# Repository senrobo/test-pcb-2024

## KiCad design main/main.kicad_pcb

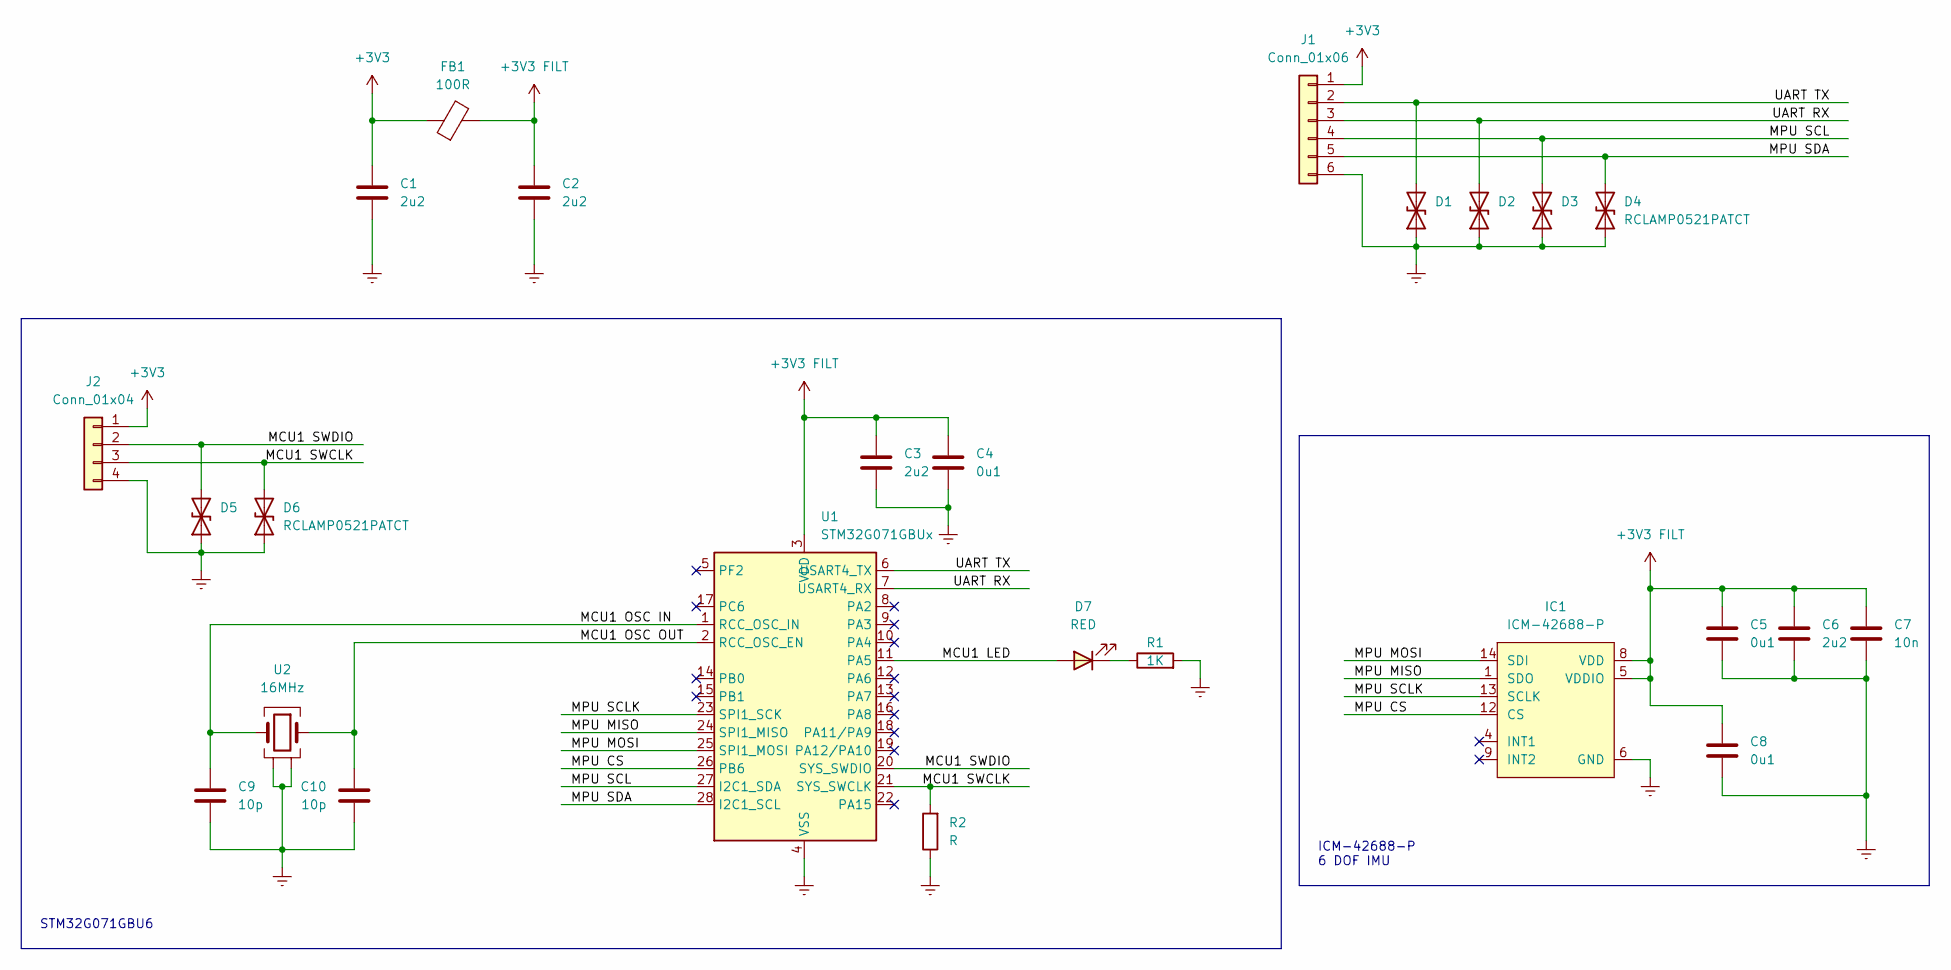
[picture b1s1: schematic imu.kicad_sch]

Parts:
C1, C2: 2u2; cap0603
C3, C6: 2u2; C_0402_1005Metric_Pad0.74x0.62mm_HandSolder
C4, C5, C8: 0u1; C_0402_1005Metric_Pad0.74x0.62mm_HandSolder
C7: 10n; C_0402_1005Metric_Pad0.74x0.62mm_HandSolder
C9, C10: 10p; C_0402_1005Metric_Pad0.74x0.62mm_HandSolder
D1, D2, D3, D4, D5, D6: RCLAMP0521PATCT
D7: RED; led0603
FB1: 100R; fb0603
IC1: ICM-42688-P; IIM42352; Mouser Part Number 410-ICM-42688-P
J1: Conn_01x06; PinHeader_1x06_P2.54mm_Vertical
J2: Conn_01x04; PinHeader_2x02_P2.54mm_Vertical
R1: 1K; R_0402_1005Metric
R2: R; R_0402_1005Metric
U1: STM32G071GBUx; QFN-28_4x4mm_P0.5mm
U2: 16MHz; 830108288709

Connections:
+3V3: C1.1, FB1.1, J1.1, J2.1
+3V3 FILT: C2.1, C3.1, C4.1, C5.1, C6.1, C7.1, C8.1, FB1.2, IC1.5 (VDDIO), IC1.8 (VDD), U1.3 (VDD)
/imu/MCU1 LED: D7.2 (A), U1.11 (PA5)
/imu/MCU1 OSC IN: C9.1, U1.1 (RCC_OSC_IN), U2.3
/imu/MCU1 OSC OUT: C10.1, U1.2 (RCC_OSC_EN), U2.1
/imu/MCU1 SWCLK: D6.2 (A2), J2.3, R2.2, U1.21 (SYS_SWCLK)
/imu/MCU1 SWDIO: D5.2 (A2), J2.2, U1.20 (SYS_SWDIO)
/imu/MPU CS: IC1.12 (CS), U1.26 (PB6)
/imu/MPU MISO: IC1.1 (SDO), U1.24 (SPI1_MISO)
/imu/MPU MOSI: IC1.14 (SDI), U1.25 (SPI1_MOSI)
/imu/MPU SCL: D3.2 (A2), J1.4, U1.27 (I2C1_SDA)
/imu/MPU SCLK: IC1.13 (SCLK), U1.23 (SPI1_SCK)
/imu/MPU SDA: D4.2 (A2), J1.5, U1.28 (I2C1_SCL)
/imu/UART RX: D2.2 (A2), J1.3, U1.7 (USART4_RX)
/imu/UART TX: D1.2 (A2), J1.2, U1.6 (USART4_TX)
GNDREF: C1.2, C2.2, C3.2, C4.2, C5.2, C6.2, C7.2, C8.2, C9.2, C10.2, D1.1 (A1), D2.1 (A1), D3.1 (A1), D4.1 (A1), D5.1 (A1), D6.1 (A1), IC1.2 (RESV), IC1.3 (RESV), IC1.6 (GND), IC1.7 (RESV), IC1.10 (RESV), IC1.11 (RESV), J1.6, J2.4, R1.2, R2.1, U1.4 (VSS), U2.2, U2.4
unnamed: D7.1 (K), R1.1

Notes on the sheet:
ICM-42688-P 6 DOF IMU
STM32G071GBU6

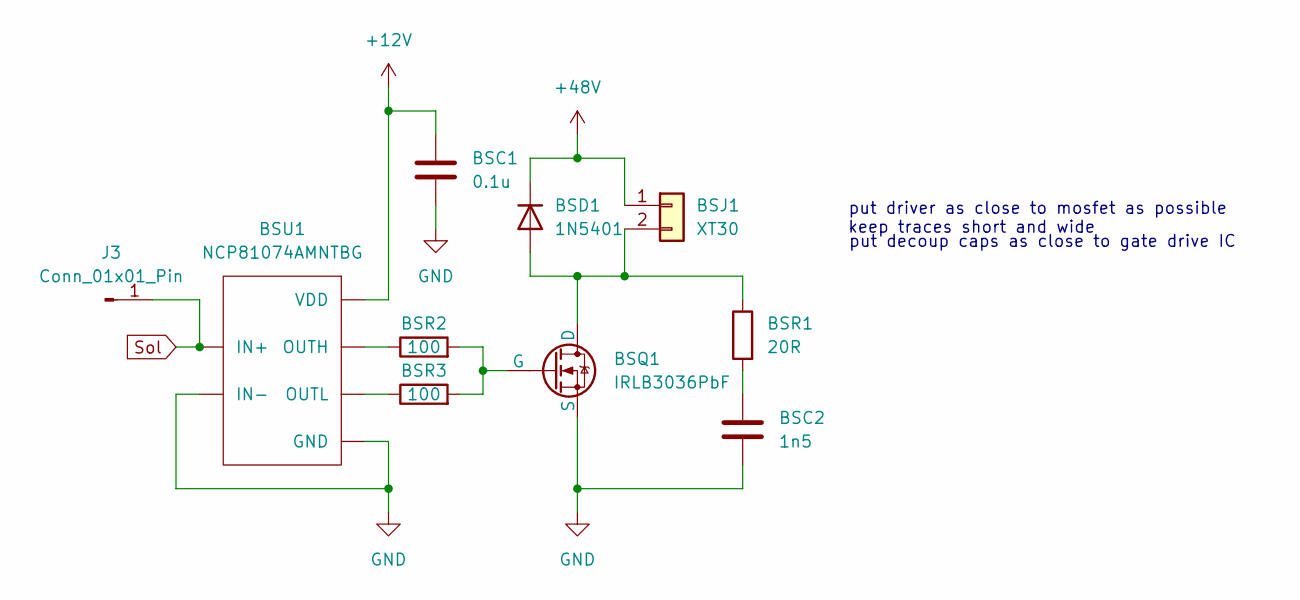
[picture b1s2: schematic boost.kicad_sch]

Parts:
BSC1: 0.1u; res0603
BSC2: 1n5; cap0603; LCSC C107060
BSD1: 1N5401; D_DO-201AD_P15.24mm_Horizontal; LCSC C179506
BSJ1: XT30; xt30-f; LCSC C108769
BSQ1: IRLB3036PbF; TO-220-3_Vertical; Mouser Part Number 726-IPD050N10N5ATMA1; LCSC C13678
BSR1: 20R; res0603; LCSC C22950
BSR2, BSR3: 100; res0603
BSU1: NCP81074AMNTBG; SON50P200X200X100-9N
J3: Conn_01x01_Pin; PinHeader_1x01_P2.54mm_Vertical

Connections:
+12V: BSC1.1, BSU1.6 (VDD), BSU1.7 (VDD)
+48V: BSD1.1 (K), BSJ1.1
GND: BSC1.2, BSC2.2, BSQ1.3 (S), BSU1.2 (GND), BSU1.3 (GND), BSU1.8 (IN-), BSU1.9 (GND)
unnamed: BSC2.1, BSR1.2
unnamed: BSD1.2 (A), BSJ1.2, BSQ1.2 (D), BSR1.1
unnamed: BSQ1.1 (G), BSR2.2, BSR3.2
unnamed: BSR2.1, BSU1.5 (OUTH)
unnamed: BSR3.1, BSU1.4 (OUTL)
Sol: BSU1.1 (IN+), J3.1

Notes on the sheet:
put decoup caps as close to gate drive IC
put driver as close to mosfet as possible
keep traces short and wide

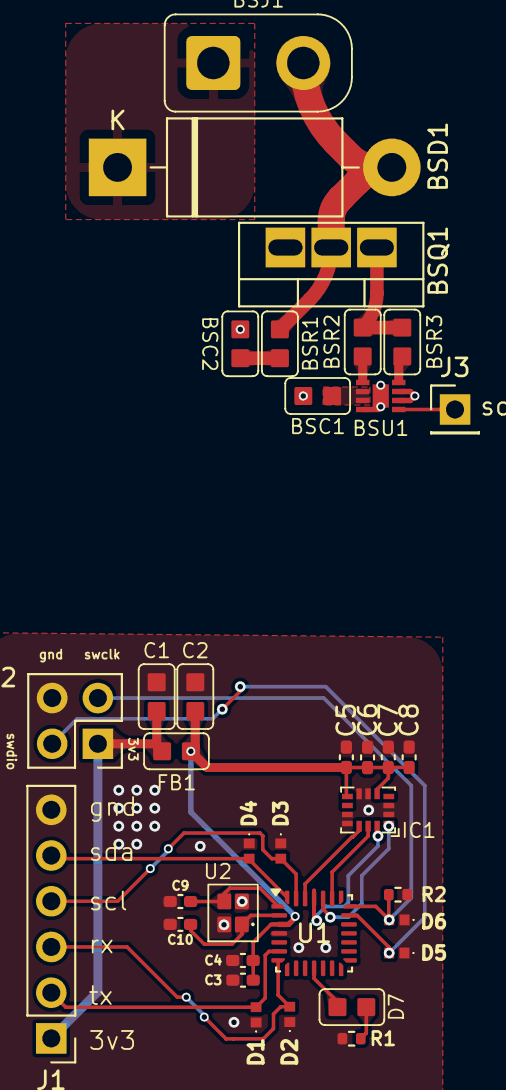
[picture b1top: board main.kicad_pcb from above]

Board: 2 copper layers, 35 parts (0 on the bottom side), 26 nets.

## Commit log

2024-10-17 Init Config
2024-10-21 cooked up a pcb layout
